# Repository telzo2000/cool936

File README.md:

# cool936

## What is cool936?

cool936 is a split keyboard with a [qaz](https://www.cbkbd.com/product/qaz-keyboard-kit) layout.
<br>
[qaz](https://www.cbkbd.com/product/qaz-keyboard-kit)レイアウトの分割キーボードです。
<br>
<br>

## Build Guide
https://github.com/telzo2000/cool936/blob/main/buildguide_for_cool936.md

<br>

## Terms of use(使用条件)

You are free to duplicate the data related to cool936, place an order for PCB, etc. and use it personally.
<br>
cool936に関するデータを複製して、PCB等発注して個人で使用するのは自由です。
<br>
However, it is prohibited to give or receive money such as sales using the data ordered by an individual.
<br>
ただし、個人で発注したデータを使用して販売等、金銭の授受が発生することは禁止です。
<br>
The transfer of money as a manufacturing agent is also included in the prohibition.
<br>
製造代行と称しての金銭の授受も禁止に含まれます。
<br>
<br>

## What are coolxxx?

These keyboards is designed by m.ki.

|cool|another name|keyboard type|MCU|URL|Sales site|
| -- | -- | -- | -- | -- | -- |
|434|MyFirstMini|row|pro micro|none|none|
|445|none|row|pro micro & Raspberry Pi Pico|[Here](https://github.com/telzo2000/cool445)|[Here](https://mki0002ozlet.booth.pm/items/4069834)|
|536|none|column|pro micro|[Here](https://github.com/telzo2000/cool536)|[Here](https://mki0002ozlet.booth.pm/items/4190386)|
|536azcore|none|colum|AZ-CORE|[Here](https://github.com/telzo2000/cool536azcore)|[Here](https://mki0002ozlet.booth.pm/items/4424562)|
|544|Caravellion|column|pro micro|none|none|
|635|none|ortho|pro micro|[Here](https://github.com/telzo2000/cool635-)|none|
|640|none|ortho splite|pro micro & Raspberry Pi Pico|[Here](https://github.com/telzo2000/cool640) |[Here](https://mki0002ozlet.booth.pm/items/3729914)|
|644|none|ortho splite|pro micro|[Here](https://github.com/telzo2000/cool644)|[Here](https://mki0002ozlet.booth.pm/items/3729914)|
|640|none|ortho splite|pro micro & Raspberry Pi Pico | [Here](https://github.com/telzo2000/cool640)|[Here](https://mki0002ozlet.booth.pm/items/3729914) |
|640|none|ortho splite|pro micro & Raspberry Pi Pico|[Here](https://github.com/telzo2000/cool640)|[Here](https://mki0002ozlet.booth.pm/items/3729914)|
|650|none|ortho splite|pro micro|[Here](https://github.com/telzo2000/cool650)|[Here](https://mki0002ozlet.booth.pm/items/3585417)|
|664|none|ortho splite|pro micro|[Here](https://github.com/telzo2000/cool664)|[Here](https://mki0002ozlet.booth.pm/items/4328726)|
|753|none|row|pro micro|none|none|
|756|none|row|pro micro|[Here](https://github.com/telzo2000/cool756)|[Here](https://mki0002ozlet.booth.pm/items/4491960)|
|836A|none|alice|pro micro|[Here](https://github.com/telzo2000/cool836A)|[Here](https://mki0002ozlet.booth.pm/items/2542223)|
|836pico|none|alice|Raspberry Pi Pico|[Here](https://github.com/telzo2000/cool836pico)|[Here](https://mki0002ozlet.booth.pm/items/3391829)|
|836rp|none|alice|RP2040-Zero|[Here](https://github.com/telzo2000/cool836pico)|[Here](https://mki0002ozlet.booth.pm/items/3599330)|
|844|none|alice|pro micro|[Here](https://github.com/telzo2000/cool844)|[Here](https://mki0002ozlet.booth.pm/items/2805606)|
|844V2|none|alice|pro micro|[Here](https://github.com/telzo2000/cool844V2)|[Here](https://mki0002ozlet.booth.pm/items/3267681)|
|847|none|alice|pro micro|[Here](https://github.com/telzo2000/cool847)|[Here](https://mki0002ozlet.booth.pm/items/3358065)|
|936|none|row splite|pro micro|[Here](https://github.com/telzo2000/cool936)|none|
|939|none|row splite|pro micro|[Here](https://github.com/telzo2000/cool939)|none|
|943S|none|row splite|pro micro|[Here](https://github.com/telzo2000/cool943S)|[Here](https://mki0002ozlet.booth.pm/items/2901779)|
|950S|none|row splite|pro micro|[Here](https://github.com/telzo2000/cool950S)|[Here](https://mki0002ozlet.booth.pm/items/3160071)|
|959|none|alice splite|pro micro|[Here](https://github.com/telzo2000/cool959)|none|

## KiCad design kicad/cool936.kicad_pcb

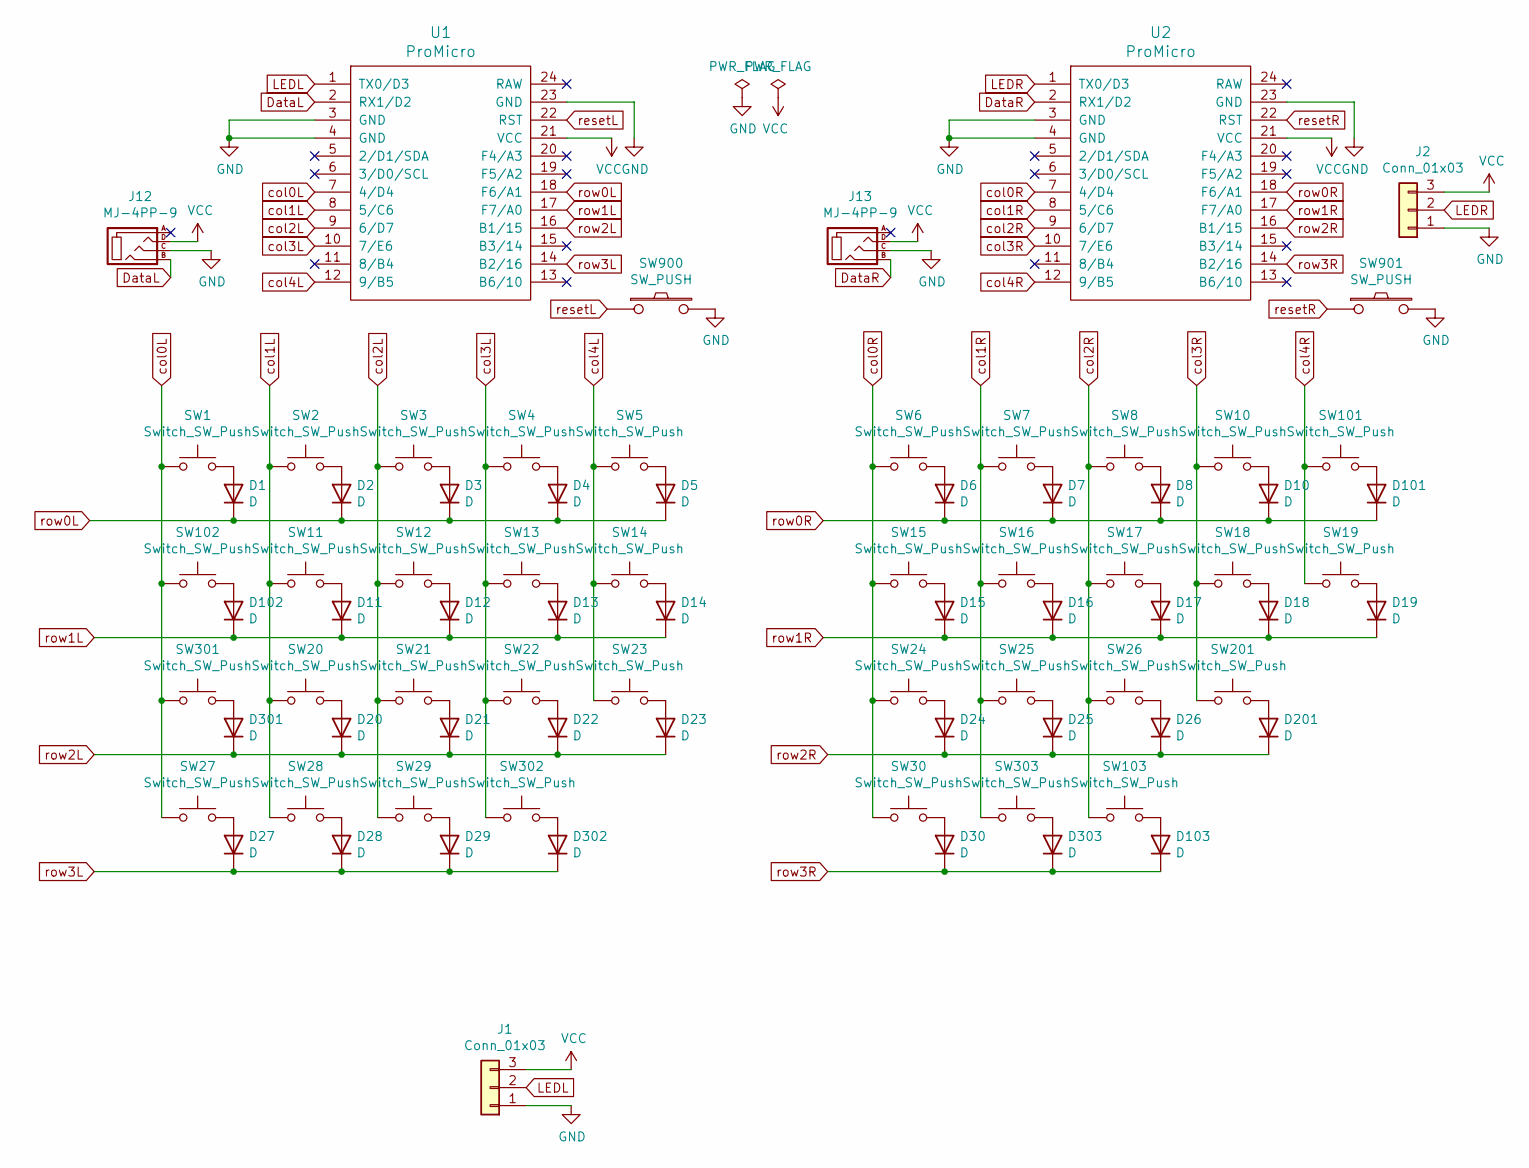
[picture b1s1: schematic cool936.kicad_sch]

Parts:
D1, D2, D3, D4, D5, D6, D7, D8, D10, D11, D12, D13, D14, D15, D16, D17, D18, D19, D20, D21, D22, D23, D24, D25, D26, D27, D28, D29, D30, D101, D102, D103, D201, D301, D302, D303: D; D3_TH_SMD
J1, J2: Conn_01x03; StripLED_1side
J12, J13: MJ-4PP-9; MJ-4PP-9_1side
SW1, SW2, SW3, SW4, SW5, SW6, SW7, SW8, SW10, SW11, SW12, SW13, SW14, SW15, SW16, SW17, SW18, SW19, SW20, SW21, SW22, SW23, SW24, SW25, SW26, SW27, SW28, SW29, SW30, SW101, SW102, SW103, SW201, SW301, SW302, SW303: Switch_SW_Push; CherryMX_Hotswap_kimura
SW900, SW901: SW_PUSH; ResetSW_1side
U1, U2: ProMicro; ProMicro_v3_kimura_for_cool936

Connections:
DataL: J12.B, U1.2 (RX1/D2)
DataR: J13.B, U2.2 (RX1/D2)
GND: J1.1, J2.1, J12.C, J13.C, SW900.2, SW901.2, U1.3 (GND), U1.4 (GND), U1.23 (GND), U2.3 (GND), U2.4 (GND), U2.23 (GND)
LEDL: J1.2, U1.1 (TX0/D3)
LEDR: J2.2, U2.1 (TX0/D3)
unnamed: D1.2 (A), SW1.2
unnamed: D2.2 (A), SW2.2
unnamed: D3.2 (A), SW3.2
unnamed: D4.2 (A), SW4.2
unnamed: D5.2 (A), SW5.2
unnamed: D6.2 (A), SW6.2
unnamed: D7.2 (A), SW7.2
unnamed: D8.2 (A), SW8.2
unnamed: D10.2 (A), SW10.2
unnamed: D11.2 (A), SW11.2
unnamed: D12.2 (A), SW12.2
unnamed: D13.2 (A), SW13.2
unnamed: D14.2 (A), SW14.2
unnamed: D15.2 (A), SW15.2
unnamed: D16.2 (A), SW16.2
unnamed: D17.2 (A), SW17.2
unnamed: D18.2 (A), SW18.2
unnamed: D19.2 (A), SW19.2
unnamed: D20.2 (A), SW20.2
unnamed: D21.2 (A), SW21.2
unnamed: D22.2 (A), SW22.2
unnamed: D23.2 (A), SW23.2
unnamed: D24.2 (A), SW24.2
unnamed: D25.2 (A), SW25.2
unnamed: D26.2 (A), SW26.2
unnamed: D27.2 (A), SW27.2
unnamed: D28.2 (A), SW28.2
unnamed: D29.2 (A), SW29.2
unnamed: D30.2 (A), SW30.2
unnamed: D101.2 (A), SW101.2
unnamed: D102.2 (A), SW102.2
unnamed: D103.2 (A), SW103.2
unnamed: D201.2 (A), SW201.2
unnamed: D301.2 (A), SW301.2
unnamed: D302.2 (A), SW302.2
unnamed: D303.2 (A), SW303.2
VCC: J1.3, J2.3, J12.D, J13.D, U1.21 (VCC), U2.21 (VCC)
col0L: SW1.1, SW27.1, SW102.1, SW301.1, U1.7 (4/D4)
col0R: SW6.1, SW15.1, SW24.1, SW30.1, U2.7 (4/D4)
col1L: SW2.1, SW11.1, SW20.1, SW28.1, U1.8 (5/C6)
col1R: SW7.1, SW16.1, SW25.1, SW303.1, U2.8 (5/C6)
col2L: SW3.1, SW12.1, SW21.1, SW29.1, U1.9 (6/D7)
col2R: SW8.1, SW17.1, SW26.1, SW103.1, U2.9 (6/D7)
col3L: SW4.1, SW13.1, SW22.1, SW302.1, U1.10 (7/E6)
col3R: SW10.1, SW18.1, SW201.1, U2.10 (7/E6)
col4L: SW5.1, SW14.1, SW23.1, U1.12 (9/B5)
col4R: SW19.1, SW101.1, U2.12 (9/B5)
resetL: SW900.1, U1.22 (RST)
resetR: SW901.1, U2.22 (RST)
row0L: D1.1 (K), D2.1 (K), D3.1 (K), D4.1 (K), D5.1 (K), U1.18 (F6/A1)
row0R: D6.1 (K), D7.1 (K), D8.1 (K), D10.1 (K), D101.1 (K), U2.18 (F6/A1)
row1L: D11.1 (K), D12.1 (K), D13.1 (K), D14.1 (K), D102.1 (K), U1.17 (F7/A0)
row1R: D15.1 (K), D16.1 (K), D17.1 (K), D18.1 (K), D19.1 (K), U2.17 (F7/A0)
row2L: D20.1 (K), D21.1 (K), D22.1 (K), D23.1 (K), D301.1 (K), U1.16 (B1/15)
row2R: D24.1 (K), D25.1 (K), D26.1 (K), D201.1 (K), U2.16 (B1/15)
row3L: D27.1 (K), D28.1 (K), D29.1 (K), D302.1 (K), U1.14 (B2/16)
row3R: D30.1 (K), D103.1 (K), D303.1 (K), U2.14 (B2/16)

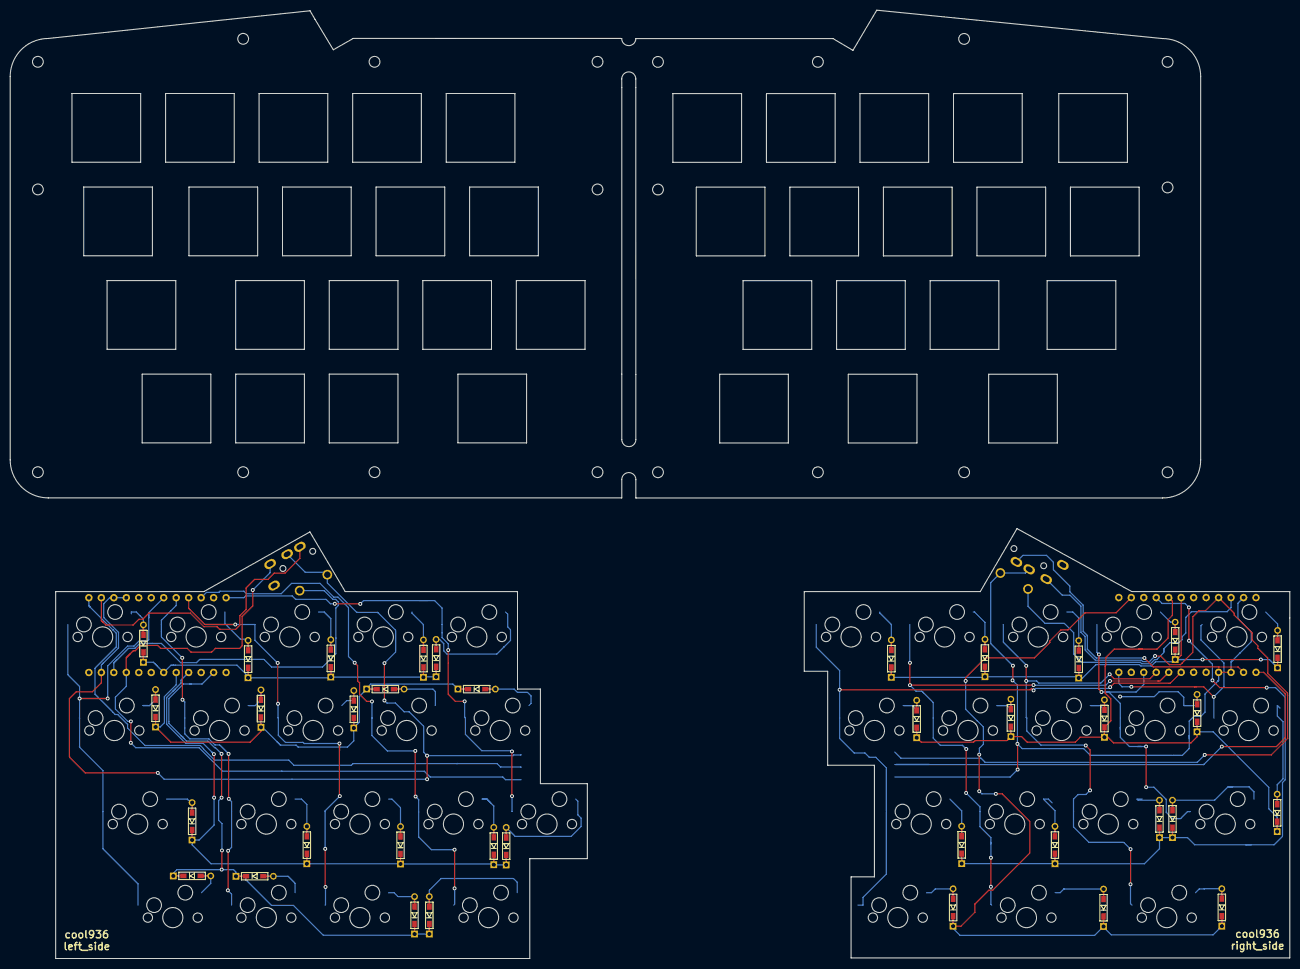
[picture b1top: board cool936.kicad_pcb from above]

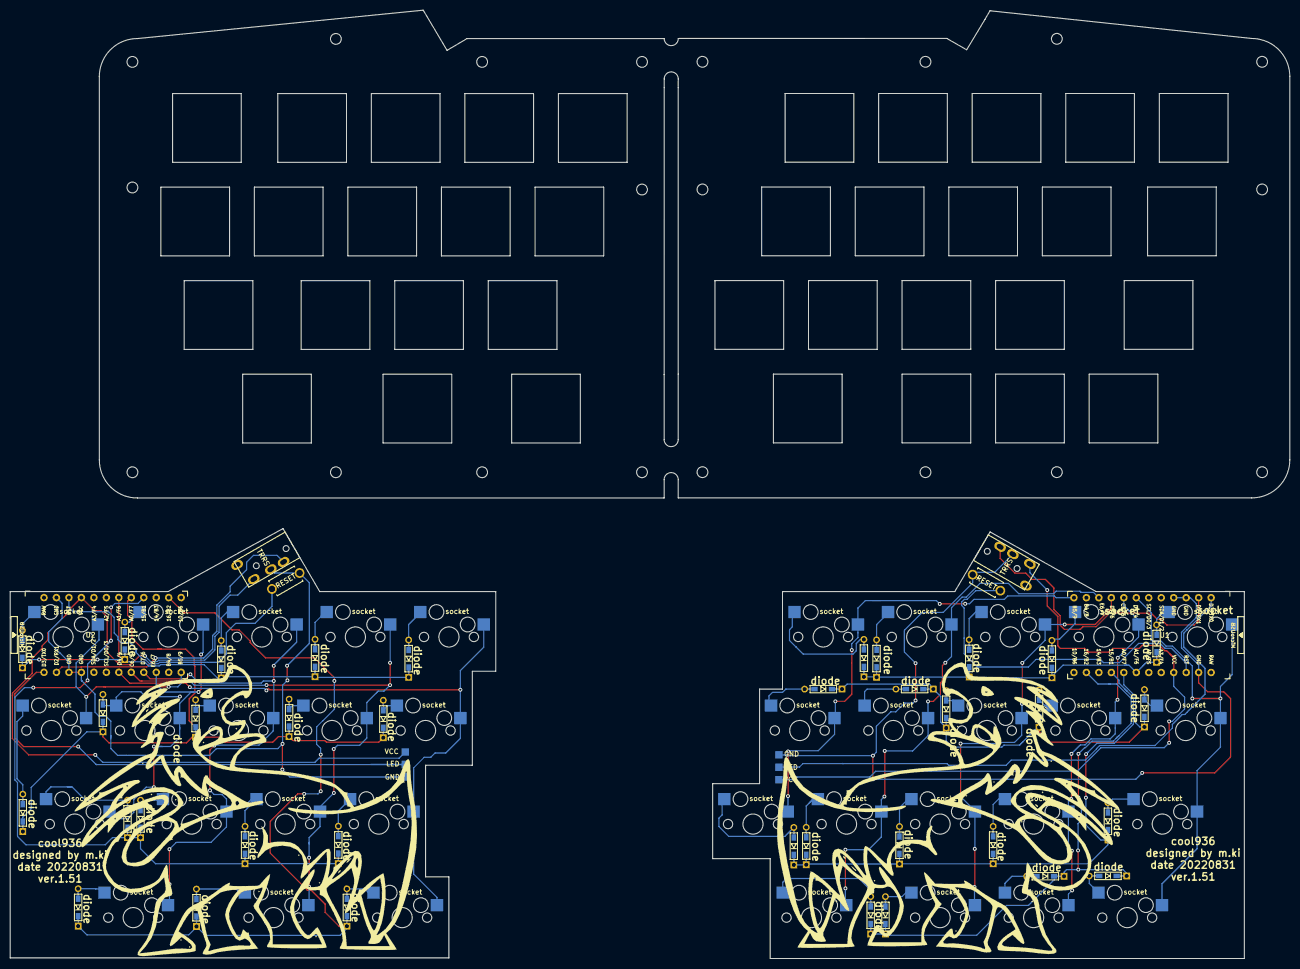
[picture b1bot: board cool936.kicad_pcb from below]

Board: 2 copper layers, 260.6 x 193.1 mm, 80 parts (6 on the bottom side), 62 nets.

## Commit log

2022-03-27 via対応
2022-04-16 fixl
